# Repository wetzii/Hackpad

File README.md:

# Hackpad V1
This is my first real try for the **Hack Club Blueprint** challenge! I wanted to build something functional and learn the full process from PCB design to 3D modeling.
**This project was guided by the Hackpad Guide**

## 1. The Idea
My goal was to create a clean and simple macro pad with the following features:
* **16 Mechanical Switches:** A full 4x4 matrix for maximum input options.
* **OLED Display:** A 0.91" screen to show status or a clock.
* **Rotary Encoder:** An EC11 knob for volume control or scrolling.
* **Simplicity:** Keeping the design beginner-friendly but powerful.

### Bill of Materials (BOM)
To build this, I am using the following components:
* **12x** 1N4148 Diodes (Through-hole).
* **12x** MX-Style Switches (Kailh Polia).
* **1x** EC11 Rotary Encoder.
* **2x** 100nF Ceramic Capacitors.
* **1x** 0.91-inch OLED Display (SSD1306).
* **12x** White Blank DSA Keycaps.
* **1x** Seeed Studio XIAO RP2040 Controller.

### Use Case
I will use it as a custom **Small Numpad**. The OLED screen will act as a system monitor or a simple clock to keep track of time while working or just to watch cool animations.

---

## 2. Schematic & Electronics
I designed the circuit to be reliable and easy to solder. It uses a row-column matrix to handle all 16 switches with the limited pins of the XIAO.

 **Important to know** 
The Rotary Encoder Switch just works to mute and unmute the Capacitor just there as backup!
I would work without the Capacitors but for me its okay.

---

## 3. PCB Design
This is the heart of the Hackpad. I routed everything carefully to fit the 4x4 grid and the extra components like the encoder and OLED.

---

## 4. 3D Modeling & Case
This was my first time 3D modeling anything! I used **Fusion 360** for the case design to ensure everything fits perfectly.

### KiCad 3D Preview
First, I checked the component placement in KiCad's 3D viewer.

### Fusion 360 Implementation
I exported the PCB as a `.step` file and imported it into Fusion 360 to build the case around it.
* **PCB Size:** 100mm x 100mm – a perfect size for a beginner like me.
* **Case Interior:** 100.5mm x 100.5mm to ensure a snug fit for the PCB.
* **Case Exterior:** 120mm x 120mm total width.
* **Switch Cutouts:** 14.2mm x 14.2mm for easy snapping of the MX switches.
* **Dimensions:** 12mm total height with a 3mm thick floor for stability.

> **Note:** The top plate might need some light sanding for a perfect fit, but I can handle these tolerances during assembly!

---

## 5. Firmware

The Crash Pad runs on **KMK Firmware** (CircuitPython).

* **Layout:** A standard Numpad layout (0–9, Backspace, Enter)
* **OLED:** Displays a custom logo and device name on a 128x32 SSD1306 display
* **Encoder:** Programmed as a System Mute toggle (works in all applications)

> **I am currently learning Python. This firmware was assisted by AI,
> but my own version is coming soon!**

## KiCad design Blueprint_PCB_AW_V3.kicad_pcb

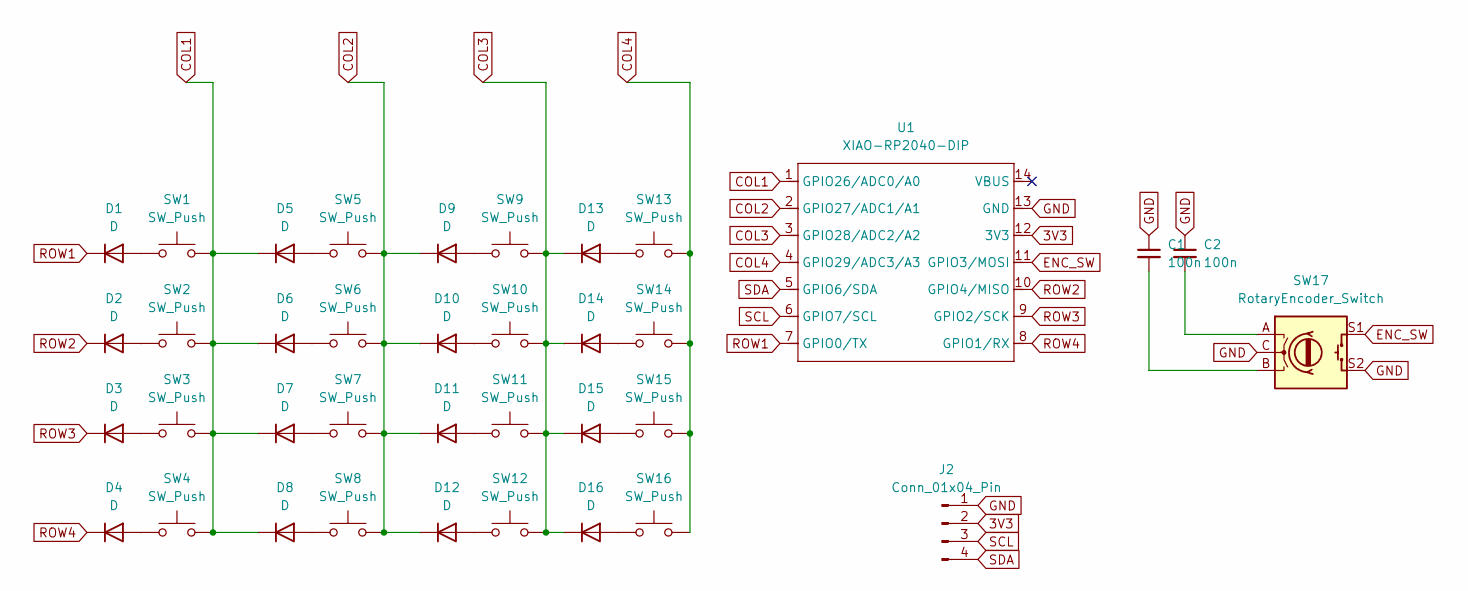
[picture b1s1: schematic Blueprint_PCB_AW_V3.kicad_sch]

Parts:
C1, C2: 100n; C_0603_1608Metric
D1, D2, D3, D4, D5, D6, D7, D8, D9, D10, D11, D12, D13, D14, D15, D16: D; D_DO-35_SOD27_P7.62mm_Horizontal
J2: Conn_01x04_Pin; SSD1306-0.91-OLED-4pin-128x32
SW1, SW2, SW3, SW4, SW5, SW6, SW7, SW8, SW9, SW10, SW11, SW12, SW13, SW14, SW15, SW16: SW_Push; SW_Cherry_MX_1.00u_PCB
SW17: RotaryEncoder_Switch; RotaryEncoder_Alps_EC11E-Switch_Vertical_H20mm_CircularMoun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
U1: XIAO-RP2040-DIP

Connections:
3V3: J2.2, U1.12 (3V3)
COL1: D5.1 (K), D6.1 (K), D7.1 (K), D8.1 (K), SW1.2, SW2.2, SW3.2, SW4.2, U1.1 (GPIO26/ADC0/A0)
COL2: D9.1 (K), D10.1 (K), D11.1 (K), D12.1 (K), SW5.2, SW6.2, SW7.2, SW8.2, U1.2 (GPIO27/ADC1/A1)
COL3: D13.1 (K), D14.1 (K), D15.1 (K), D16.1 (K), SW9.2, SW10.2, SW11.2, SW12.2, U1.3 (GPIO28/ADC2/A2)
COL4: SW13.2, SW14.2, SW15.2, SW16.2, U1.4 (GPIO29/ADC3/A3)
ENC_SW: SW17.S1, U1.11 (GPIO3/MOSI)
GND: C1.1, C2.1, J2.1, SW17.C, SW17.S2, U1.13 (GND)
unnamed: C1.2, SW17.B
unnamed: C2.2, SW17.A
unnamed: D1.2 (A), SW1.1
unnamed: D2.2 (A), SW2.1
unnamed: D3.2 (A), SW3.1
unnamed: D4.2 (A), SW4.1
unnamed: D5.2 (A), SW5.1
unnamed: D6.2 (A), SW6.1
unnamed: D7.2 (A), SW7.1
unnamed: D8.2 (A), SW8.1
unnamed: D9.2 (A), SW9.1
unnamed: D10.2 (A), SW10.1
unnamed: D11.2 (A), SW11.1
unnamed: D12.2 (A), SW12.1
unnamed: D13.2 (A), SW13.1
unnamed: D14.2 (A), SW14.1
unnamed: D15.2 (A), SW15.1
unnamed: D16.2 (A), SW16.1
ROW1: D1.1 (K), U1.7 (GPIO0/TX)
ROW2: D2.1 (K), U1.10 (GPIO4/MISO)
ROW3: D3.1 (K), U1.9 (GPIO2/SCK)
ROW4: D4.1 (K), U1.8 (GPIO1/RX)
SCL: J2.3, U1.6 (GPIO7/SCL)
SDA: J2.4, U1.5 (GPIO6/SDA)

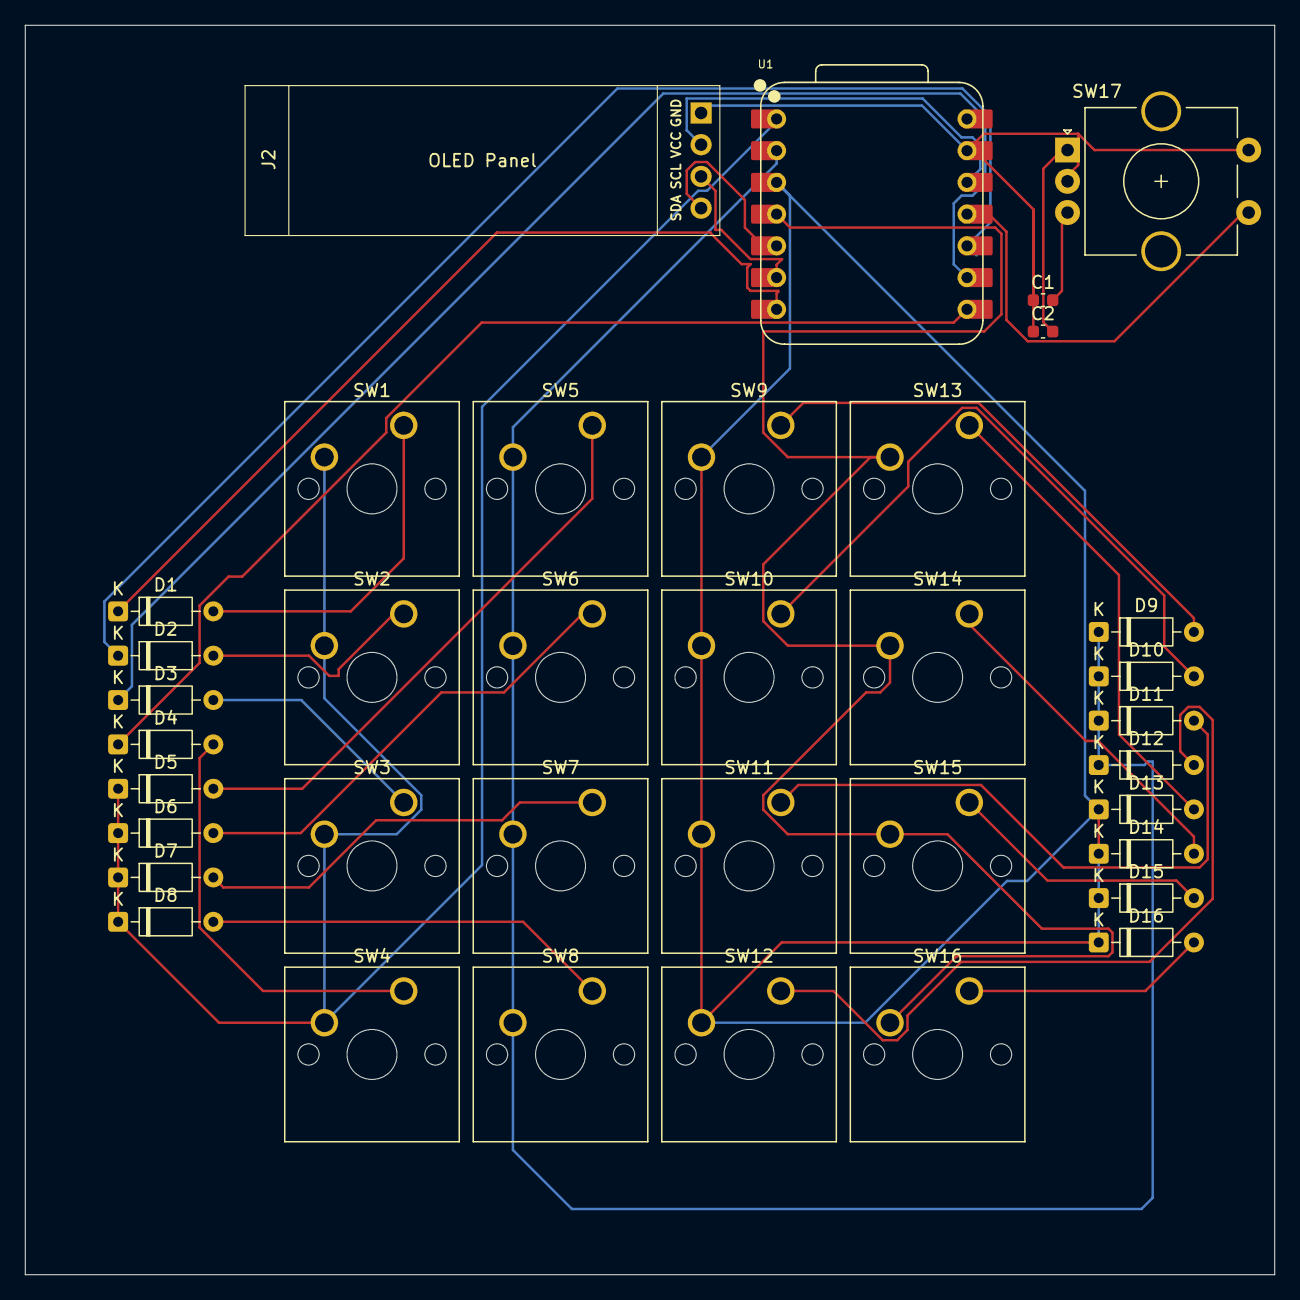
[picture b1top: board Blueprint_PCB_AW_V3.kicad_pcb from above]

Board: 2 copper layers, 100.0 x 100.0 mm, 37 parts (0 on the bottom side), 31 nets.

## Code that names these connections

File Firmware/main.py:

import board
import busio
import displayio
import terminalio
from adafruit_display_text import label
import adafruit_displayio_ssd1306

from kmk.kmk_keyboard import KMKKeyboard
from kmk.keys import KC
from kmk.scanners.keypad import KeysScanner
from kmk.scanners import DiodeOrientation
from kmk.matrix import KeyMatrix
from kmk.modules.encoder import EncoderHandler
from kmk.extensions.media_keys import MediaKeys

# ─────────────────────────────────────────────
#  OLED Setup (I2C: SDA=GPIO6, SCL=GPIO7)
# ─────────────────────────────────────────────
displayio.release_displays()

i2c = busio.I2C(scl=board.GPIO7, sda=board.GPIO6)
display_bus = displayio.I2CDisplay(i2c, device_address=0x3C)
display = adafruit_displayio_ssd1306.SSD1306(display_bus, width=128, height=32)

# Splash Screen
splash = displayio.Group()
display.show(splash)

# Hintergrund schwarz
bg_bitmap = displayio.Bitmap(128, 32, 1)
bg_palette = displayio.Palette(1)
bg_palette[0] = 0x000000
bg_sprite = displayio.TileGrid(bg_bitmap, pixel_shader=bg_palette, x=0, y=0)
splash.append(bg_sprite)

# Zeile 1: Großer Text
line1 = label.Label(
    terminalio.FONT,
    text="  NUMPAD PRO",
    color=0xFFFFFF,
    x=0,
    y=8,
    scale=1,
)
splash.append(line1)

# Zeile 2: Kleiner Untertitel
line2 = label.Label(
    terminalio.FONT,
    text=" XIAO RP2040 KMK",
    color=0xFFFFFF,
    x=0,
    y=22,
    scale=1,
)
splash.append(line2)

# ─────────────────────────────────────────────
#  Keyboard Setup
# ─────────────────────────────────────────────
keyboard = KMKKeyboard()

# Matrix: 4 Zeilen x 3 Spalten
# ROW1=GPIO0, ROW2=GPIO4, ROW3=GPIO2, ROW4=GPIO1
# COL1=GPIO26, COL2=GPIO27, COL3=GPIO28
keyboard.matrix = KeyMatrix(
    row_pins=(board.GPIO0, board.GPIO4, board.GPIO2, board.GPIO1),
    col_pins=(board.GPIO26, board.GPIO27, board.GPIO28),
    diode_orientation=DiodeOrientation.ROW2COL,
)

# ─────────────────────────────────────────────
#  Media Keys Extension (für MUTE)
# ─────────────────────────────────────────────
keyboard.extensions.append(MediaKeys())

# ─────────────────────────────────────────────
#  Rotary Encoder (nur Button - GPIO3)
#  Drehfunktion NICHT angeschlossen → nur SW (Mute Toggle)
# ─────────────────────────────────────────────
encoder_handler = EncoderHandler()
encoder_handler.pins = ((board.GPIO3, None, None, True),)  # (SW, A, B, pullup)
encoder_handler.map = [
    # (drehen links, drehen rechts, drücken)
    ((KC.NO, KC.NO, KC.MUTE),),
]
keyboard.modules.append(encoder_handler)

# ─────────────────────────────────────────────
#  Keymap
#  Layout laut PCB (Bild 3):
#
#  ROW1: SW1=7   SW5=9   SW9=3
#  ROW2: SW2=4   SW6=5   SW10=BSPC
#  ROW3: SW3=1   SW7=6   SW11=ENTER  (SW11 fehlt → SW7=9? → Nein, lt. Bestätigung)
#  ROW4: SW4=8   SW8=?   SW12=0
#
#  Korrigiertes Layout nach Bestätigung:
#  ROW1: SW1=7,  SW5=9,  SW9=3
#  ROW2: SW2=4,  SW6=5,  SW10=BSPC
#  ROW3: SW3=1,  SW7=6,  SW11=ENTER
#  ROW4: SW4=8,  SW8=2,  SW12=0     (SW8 laut Bild = 6... aber SW6=5, SW9=3)
#
#  Finales bestätigtes Layout:
#  Spalte:   COL1    COL2    COL3
#  ROW1:     SW1=7   SW5=9   SW9=3
#  ROW2:     SW2=4   SW6=5   SW10=BSPC
#  ROW3:     SW3=1   SW7=6   SW11=ENT
#  ROW4:     SW4=8   SW8=2   SW12=0
# ─────────────────────────────────────────────
keyboard.keymap = [
    [
        # ROW1
        KC.N7,    KC.N9,    KC.N3,
        # ROW2
        KC.N4,    KC.N5,    KC.BSPC,
        # ROW3
        KC.N1,    KC.N6,    KC.ENT,
        # ROW4
        KC.N8,    KC.N2,    KC.N0,
    ]
]

if __name__ == "__main__":
    keyboard.go()

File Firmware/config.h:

// Copyright 2024 Hackpad
// SPDX-License-Identifier: GPL-2.0-or-later

#pragma once

// -------------------------------------------------------------------------
// XIAO RP2040 DIP - Pin Mapping
// Pin 1  = GP26 = COL1
// Pin 2  = GP27 = COL2
// Pin 3  = GP28 = COL3
// Pin 4  = GP29 = COL4
// Pin 5  = GP6  = SDA (OLED)
// Pin 6  = GP7  = SCL (OLED)
// Pin 7  = GP0  = ROW1
// Pin 8  = GP1  = ROW4
// Pin 9  = GP2  = ROW3
// Pin 10 = GP4  = ROW2
// Pin 11 = GP3  = ENC_SW (nur Taster)
// -------------------------------------------------------------------------

#define I2C1_SDA_PIN GP6
#define I2C1_SCL_PIN GP7
#define I2C1_CLOCK_SPEED 400000

#define OLED_DISPLAY_128X32
#define OLED_TIMEOUT 30000
#define OLED_I2C_ADDRESS 0x3C

#define DEBOUNCE 5

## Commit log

2026-03-02 Create Hackpad PCB --> Connects arent here right now
2026-03-02 Just a few Screenshots for you
2026-03-03 Work on PCB Finish V1
2026-03-03 Just updates in README
2026-03-04 Finished PCB
2026-03-04 Work in README and comment smth
2026-03-04 Few tries to 3D Model absolutly not Finished but PCB is 100 % ready
2026-03-05 big changes in Structur Finished Full Case design -> I just have to split it
2026-03-07 Changes in Read me + Firmware + CAD Complete
2026-03-07 Screenshot
2026-03-07 Workflow
2026-03-07 Add GitHub Actions workflow for building Hackpad UF2
2026-03-07 Update GitHub Actions workflow for artifact upload
2026-03-07 Update CMake command to include firmware subfolder
    Specify the subfolder for CMakeLists.txt in the build step.
2026-03-07 Update CMake command in workflow
    Simplified CMake command by removing unnecessary path.
2026-03-07 structure
2026-03-07 Add GitHub Actions workflow for QMK firmware build
2026-03-07 Update GitHub Actions workflow for QMK build
2026-03-07 replace build
2026-03-07 Update GitHub Actions workflow for firmware build
2026-03-08 changes2
2026-03-08 I hope it createsy uf2
2026-03-10 big changes I lowkey designed new board
2026-03-10 changes in readMe and Structure
2026-03-10 Added Firmware to Production and changed in readME
2026-03-11 Changed Formwork plan to real one
